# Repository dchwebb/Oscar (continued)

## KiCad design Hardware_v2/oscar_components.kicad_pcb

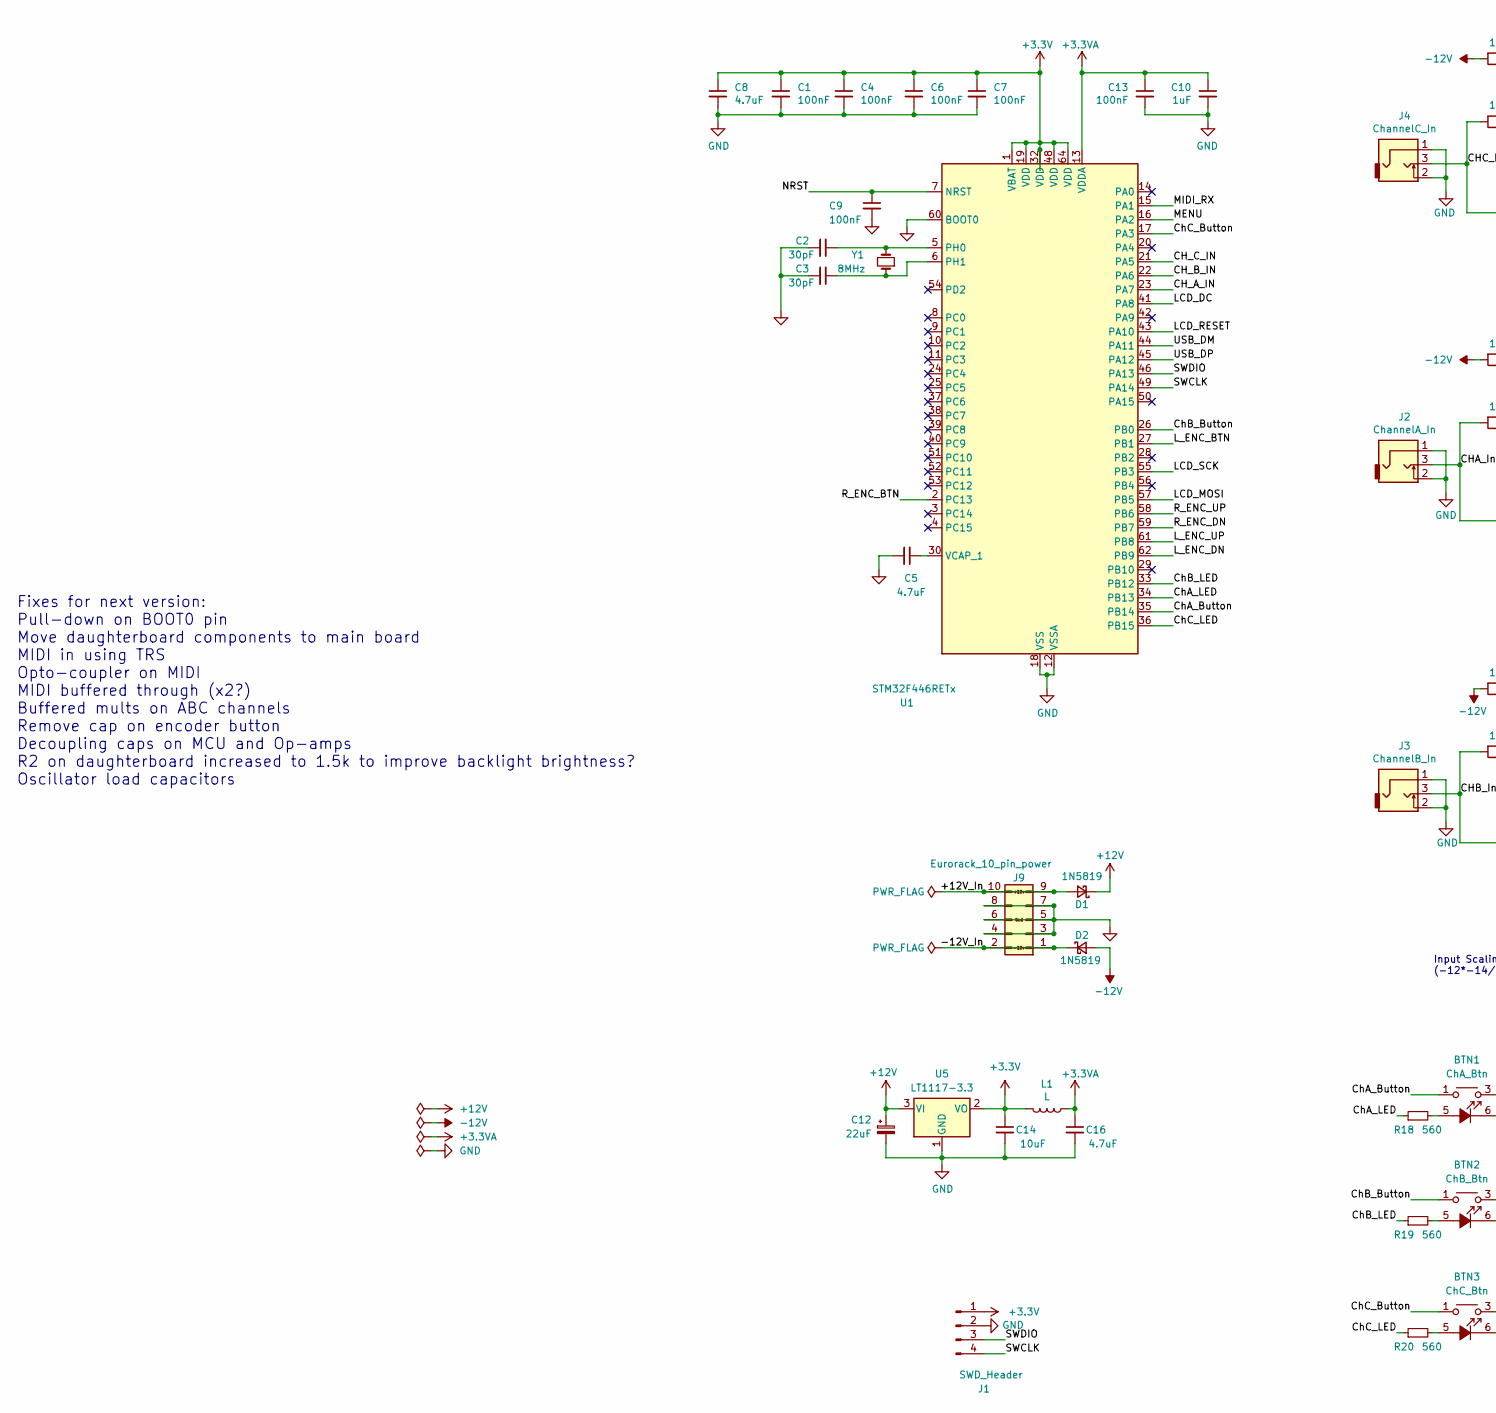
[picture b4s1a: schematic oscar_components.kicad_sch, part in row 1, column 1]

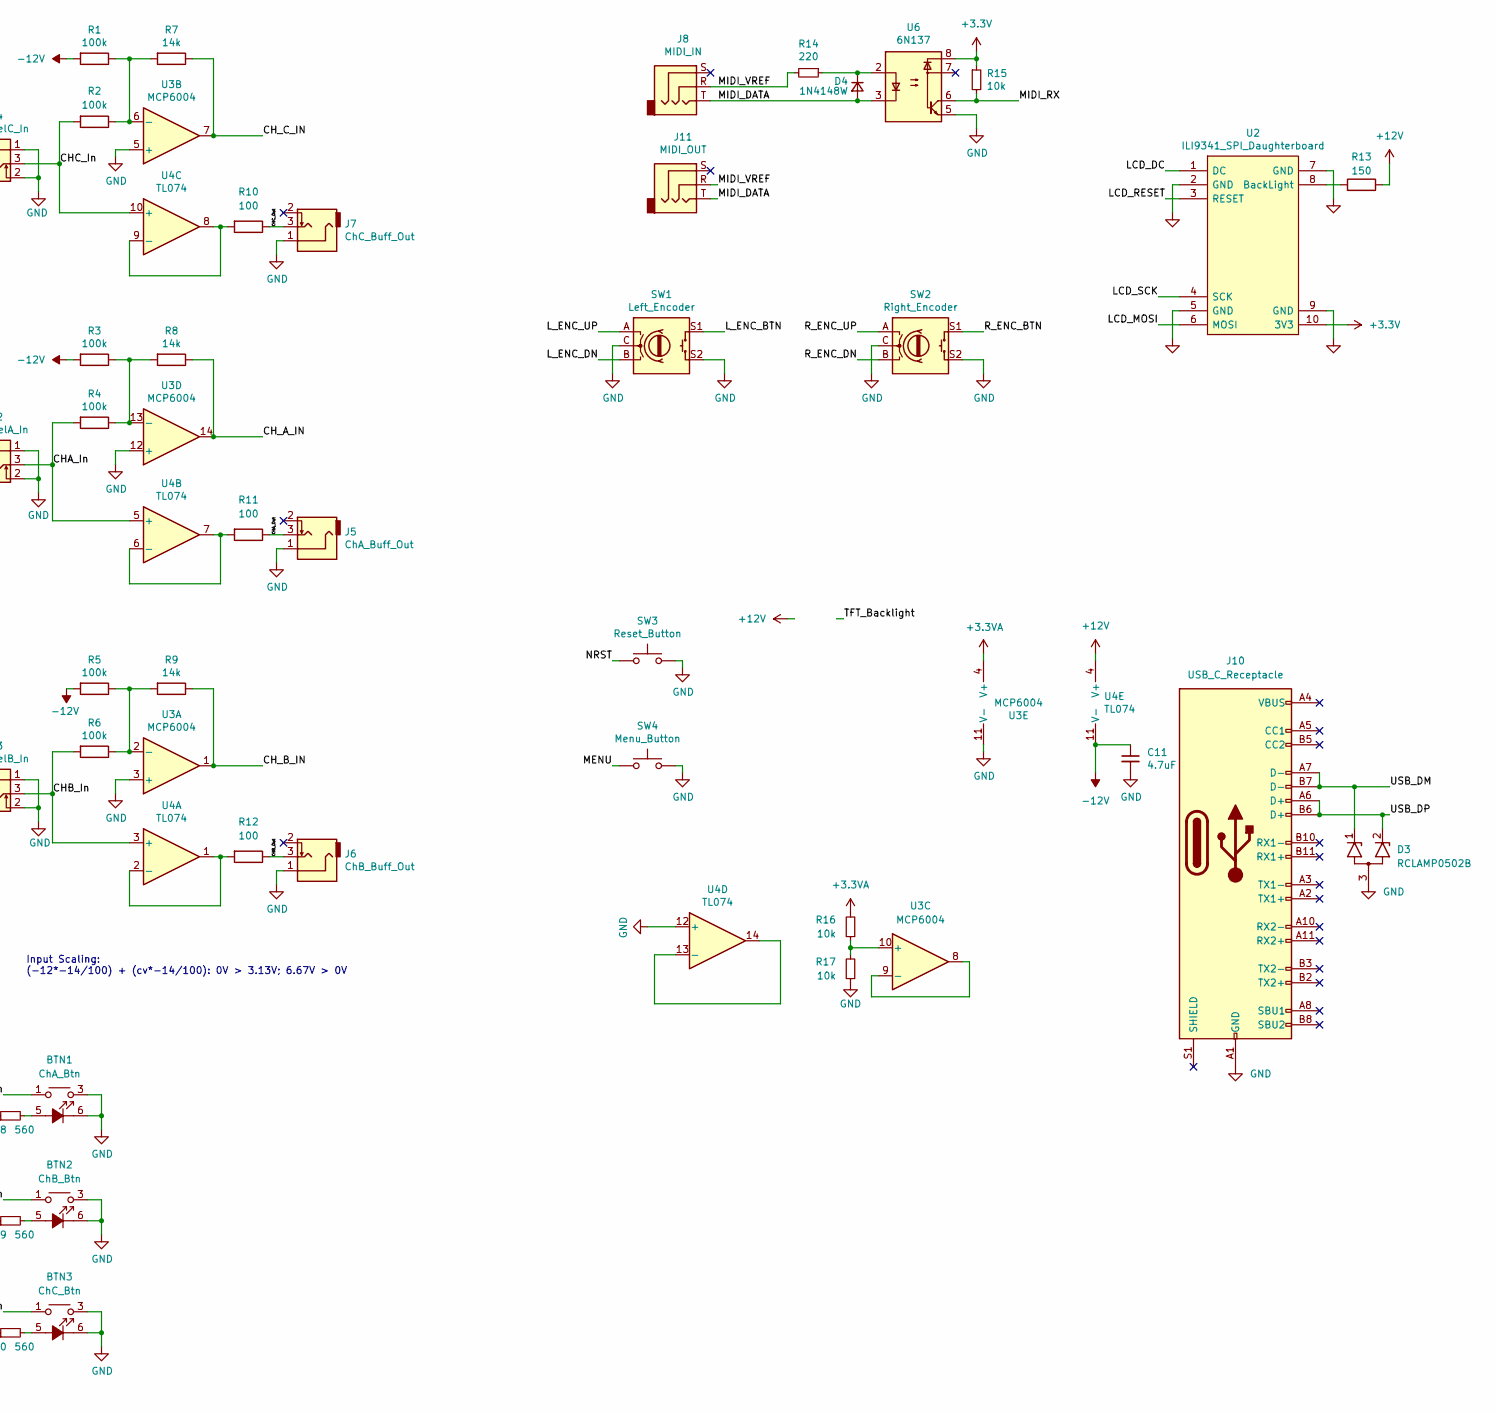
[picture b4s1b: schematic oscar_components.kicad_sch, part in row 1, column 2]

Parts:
BTN1: ChA_Btn; Low_Profile_LED_Button
BTN2: ChB_Btn; Low_Profile_LED_Button
BTN3: ChC_Btn; Low_Profile_LED_Button
C1, C4, C6, C7, C9, C13: 100nF; C_0805_2012Metric
C2, C3: 30pF; C_0805_2012Metric
C5, C8, C11, C16: 4.7uF; C_0805_2012Metric
C10: 1uF; C_0805_2012Metric
C12: 22uF; CP_Elec_4x5.8
C14: 10uF; CP_Elec_4x5.8
D1, D2: 1N5819; D_SOD-123
D3: RCLAMP0502B; SOT-416
D4: 1N4148W; D_SOD-123
J1: SWD_Header; SWD_header
J2: ChannelA_In; THONKICONN_hole
J3: ChannelB_In; THONKICONN_hole
J4: ChannelC_In; THONKICONN_hole
J5: ChA_Buff_Out; THONKICONN_hole
J6: ChB_Buff_Out; THONKICONN_hole
J7: ChC_Buff_Out; THONKICONN_hole
J8: MIDI_IN; Thonkiconn_Stereo-PJ366ST
J9: Eurorack_10_pin_power; Eurorack_10_pin_header
J10: USB_C_Receptacle; USB_C_Receptacle_Amphenol_12401951E412A
J11: MIDI_OUT; Thonkiconn_Stereo-PJ366ST
L1: L; R_0805_2012Metric
R1, R2, R3, R4, R5, R6: 100k; R_0805_2012Metric
R7, R8, R9: 14k; R_0805_2012Metric
R10, R11, R12: 100; R_0805_2012Metric
R13: 150; R_0805_2012Metric
R14: 220; R_0805_2012Metric
R15: 10k; R_0805_2012Metric
R16, R17: 10k; R_0805_2012Metric; Part_Number C23162
R18, R19, R20: 560; R_0805_2012Metric; Part_Number C23162
SW1: Left_Encoder; Encoder
SW2: Right_Encoder; Encoder
SW3: Reset_Button; SW_PUSH_6mm
SW4: Menu_Button; SW_PUSH_6mm
U1: STM32F446RETx; LQFP-64_10x10mm_P0.5mm
U2: ILI9341_SPI_Daughterboard; ILI9341_SPI_daughterboard_v2
U3: MCP6004; SOIC-14_3.9x8.7mm_P1.27mm
U4: TL074; SOIC-14_3.9x8.7mm_P1.27mm
U5: LT1117-3.3; SOT-223-3_TabPin2
U6: 6N137; DIP-8_W8.89mm_SMDSocket_LongPads
Y1: 8MHz; Crystal_SMD_Abracon_ABM3-2Pin_5.0x3.2mm

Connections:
+3.3V: C1.1, C4.1, C6.1, C7.1, C8.1, C14.1, J1.1, L1.2, R15.1, U1.1 (VBAT), U1.19 (VDD), U1.32 (VDD), U1.48 (VDD), U1.64 (VDD), U2.10 (3V3), U5.2 (VO), U6.8
+3.3VA: C10.1, C13.1, C16.1, L1.1, R16.2, U1.13 (VDDA), U3.4 (V+)
+12V: C12.1, D1.1 (K), R13.1, U4.4 (V+), U5.3 (VI)
-12V: C11.1, D2.2 (A), R1.2, R3.2, R5.2, U4.11 (V-)
/+12V_In: D1.2 (A), J9.9, J9.10
/-12V_In: D2.1 (K), J9.1, J9.2
/CHA_In: J2.3, R4.2, U4.5 (+)
/CHA_Out: J5.3, R11.1
/CHB_In: J3.3, R6.2, U4.3 (+)
/CHB_Out: J6.3, R12.1
/CHC_In: J4.3, R2.2, U4.10 (+)
/CHC_Out: J7.3, R10.1
/CH_A_IN: R8.1, U1.23 (PA7), U3.14
/CH_B_IN: R9.1, U1.22 (PA6), U3.1
/CH_C_IN: R7.1, U1.21 (PA5), U3.7
/ChA_Button: BTN1.1, BTN1.2, U1.35 (PB14)
/ChA_LED: R18.1, U1.34 (PB13)
/ChB_Button: BTN2.1, BTN2.2, U1.26 (PB0)
/ChB_LED: R19.1, U1.33 (PB12)
/ChC_Button: BTN3.1, BTN3.2, U1.17 (PA3)
/ChC_LED: R20.1, U1.36 (PB15)
/LCD_DC: U1.41 (PA8), U2.1 (DC)
/LCD_MOSI: U1.57 (PB5), U2.6 (MOSI)
/LCD_RESET: U1.43 (PA10), U2.3 (RESET)
/LCD_SCK: U1.55 (PB3), U2.4 (SCK)
/L_ENC_BTN: SW1.S1, U1.27 (PB1)
/L_ENC_DN: SW1.B, U1.62 (PB9)
/L_ENC_UP: SW1.A, U1.61 (PB8)
/MENU: SW4.1, U1.16 (PA2)
/MIDI_DATA: D4.2 (A), J8.T, J11.T, U6.3
/MIDI_RX: R15.2, U1.15 (PA1), U6.6
/MIDI_VREF: J8.R, J11.R, R14.2
/NRST: C9.1, SW3.1, U1.7 (NRST)
/R_ENC_BTN: SW2.S1, U1.2 (PC13)
/R_ENC_DN: SW2.B, U1.59 (PB7)
/R_ENC_UP: SW2.A, U1.58 (PB6)
/SWCLK: J1.4, U1.49 (PA14)
/SWDIO: J1.3, U1.46 (PA13)
/USB_DM: D3.1 (K1), J10.A7 (D-), J10.B7 (D-), U1.44 (PA11)
/USB_DP: D3.2 (K2), J10.A6 (D+), J10.B6 (D+), U1.45 (PA12)
GND: BTN1.3, BTN1.4, BTN1.6 (K), BTN2.3, BTN2.4, BTN2.6 (K), BTN3.3, BTN3.4, BTN3.6 (K), C1.2, C2.2, C3.2, C4.2, C5.2, C6.2, C7.2, C8.2, C9.2, C10.2, C11.2, C12.2, C13.2, C14.2, C16.2, D3.3 (A), J1.2, J2.1, J2.2, J3.1, J3.2, J4.1, J4.2, J5.1, J6.1, J7.1, J9.3, J9.4, J9.5, J9.6, J9.7, J9.8, J10.A1 (GND), J10.A12 (GND), J10.B1 (GND), J10.B12 (GND), R17.1, SW1.C, SW1.S2, SW2.C, SW2.S2, SW3.2, SW4.2, U1.12 (VSSA), U1.18 (VSS), U1.31 (VSS), U1.47 (VSS), U1.60 (BOOT0), U1.63 (VSS), U2.2 (GND), U2.5 (GND), U2.7 (GND), U2.9 (GND), U3.3 (+), U3.5 (+), U3.11 (V-), U3.12 (+), U4.12 (+), U5.1 (GND), U6.5
unnamed: BTN1.5 (A), R18.2
unnamed: BTN2.5 (A), R19.2
unnamed: BTN3.5 (A), R20.2
unnamed: D4.1 (K), R14.1, U6.2
unnamed: C2.1, U1.5 (PH0), Y1.2
unnamed: C3.1, U1.6 (PH1), Y1.1
unnamed: C5.1, U1.30 (VCAP_1)
unnamed: R13.2, U2.8 (BackLight)
unnamed: R5.1, R6.1, R9.2, U3.2 (-)
unnamed: R1.1, R2.1, R7.2, U3.6 (-)
unnamed: R16.1, R17.2, U3.10 (+)
unnamed: U3.8, U3.9 (-)
unnamed: R3.1, R4.1, R8.2, U3.13 (-)
unnamed: R12.2, U4.1, U4.2 (-)
unnamed: R11.2, U4.6 (-), U4.7
unnamed: R10.2, U4.8, U4.9 (-)
unnamed: U4.13 (-), U4.14

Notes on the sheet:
Input Scaling: (-12*-14/100) + (cv*-14/100): 0V > 3.13V; 6.67V > 0V
Fixes for next version: Pull-down on BOOT0 pin Move daughterboard components to main board MIDI in using TRS Opto-coupler on MIDI MIDI buffered through (x2?) Buffered mults on ABC channels Remove cap on encoder button Decoupling caps on MCU and Op-amps R2 on daughterboard increased to 1.5k to impro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

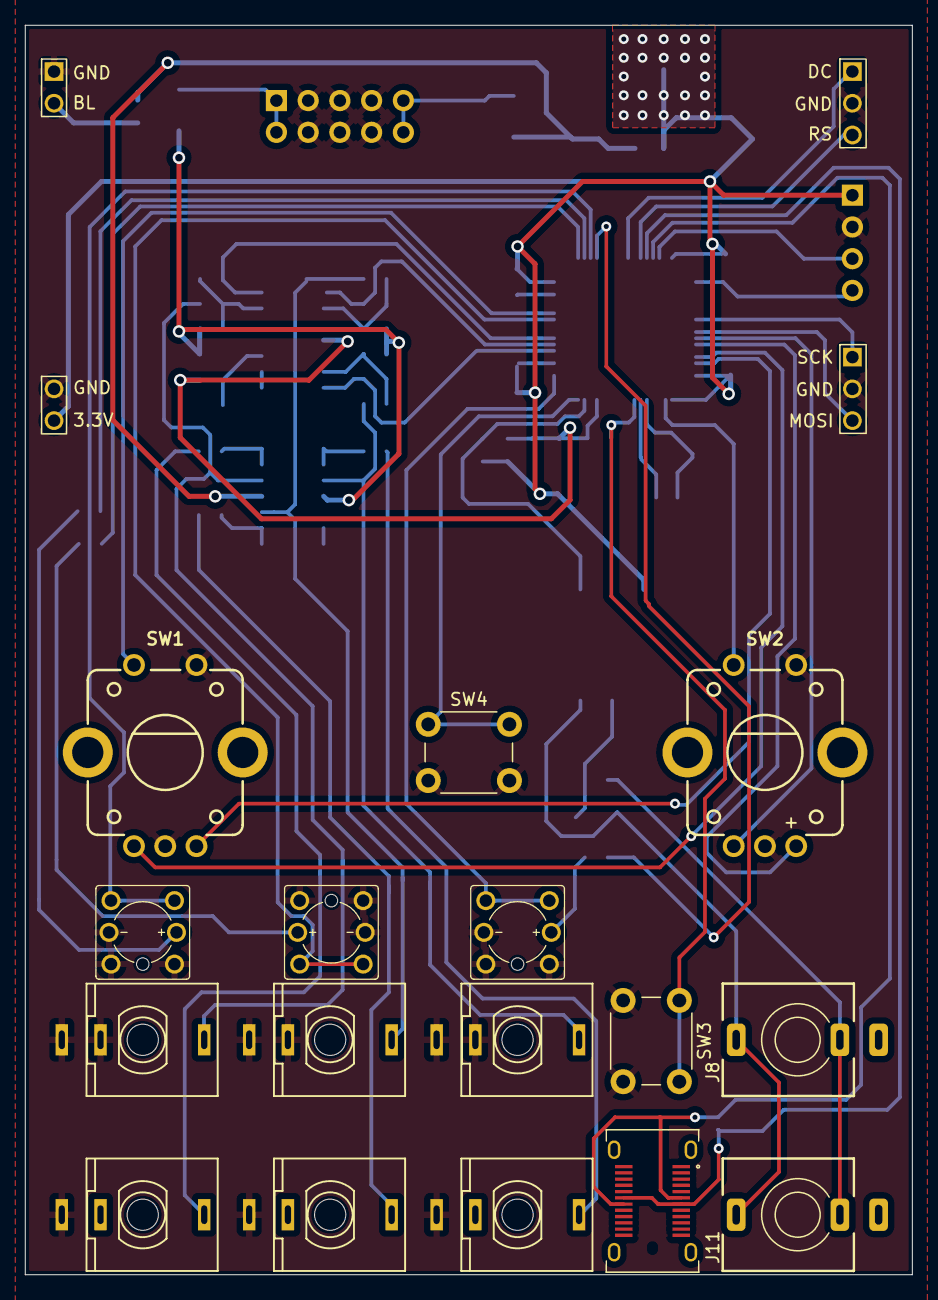
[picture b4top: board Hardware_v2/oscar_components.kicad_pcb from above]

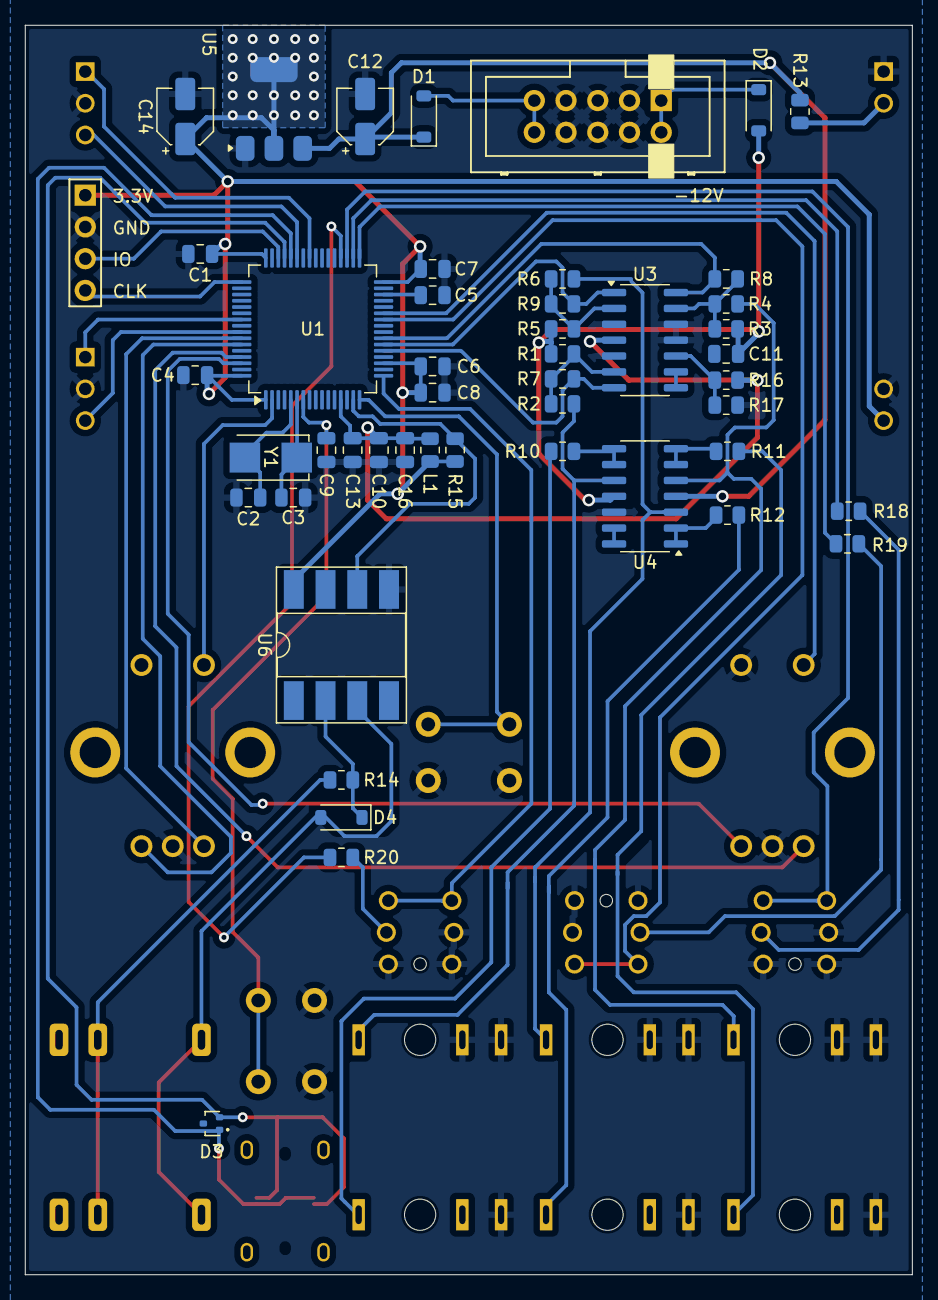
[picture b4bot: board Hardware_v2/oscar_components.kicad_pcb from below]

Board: 4 copper layers, 71.0 x 100.0 mm, 65 parts (48 on the bottom side), 58 nets.

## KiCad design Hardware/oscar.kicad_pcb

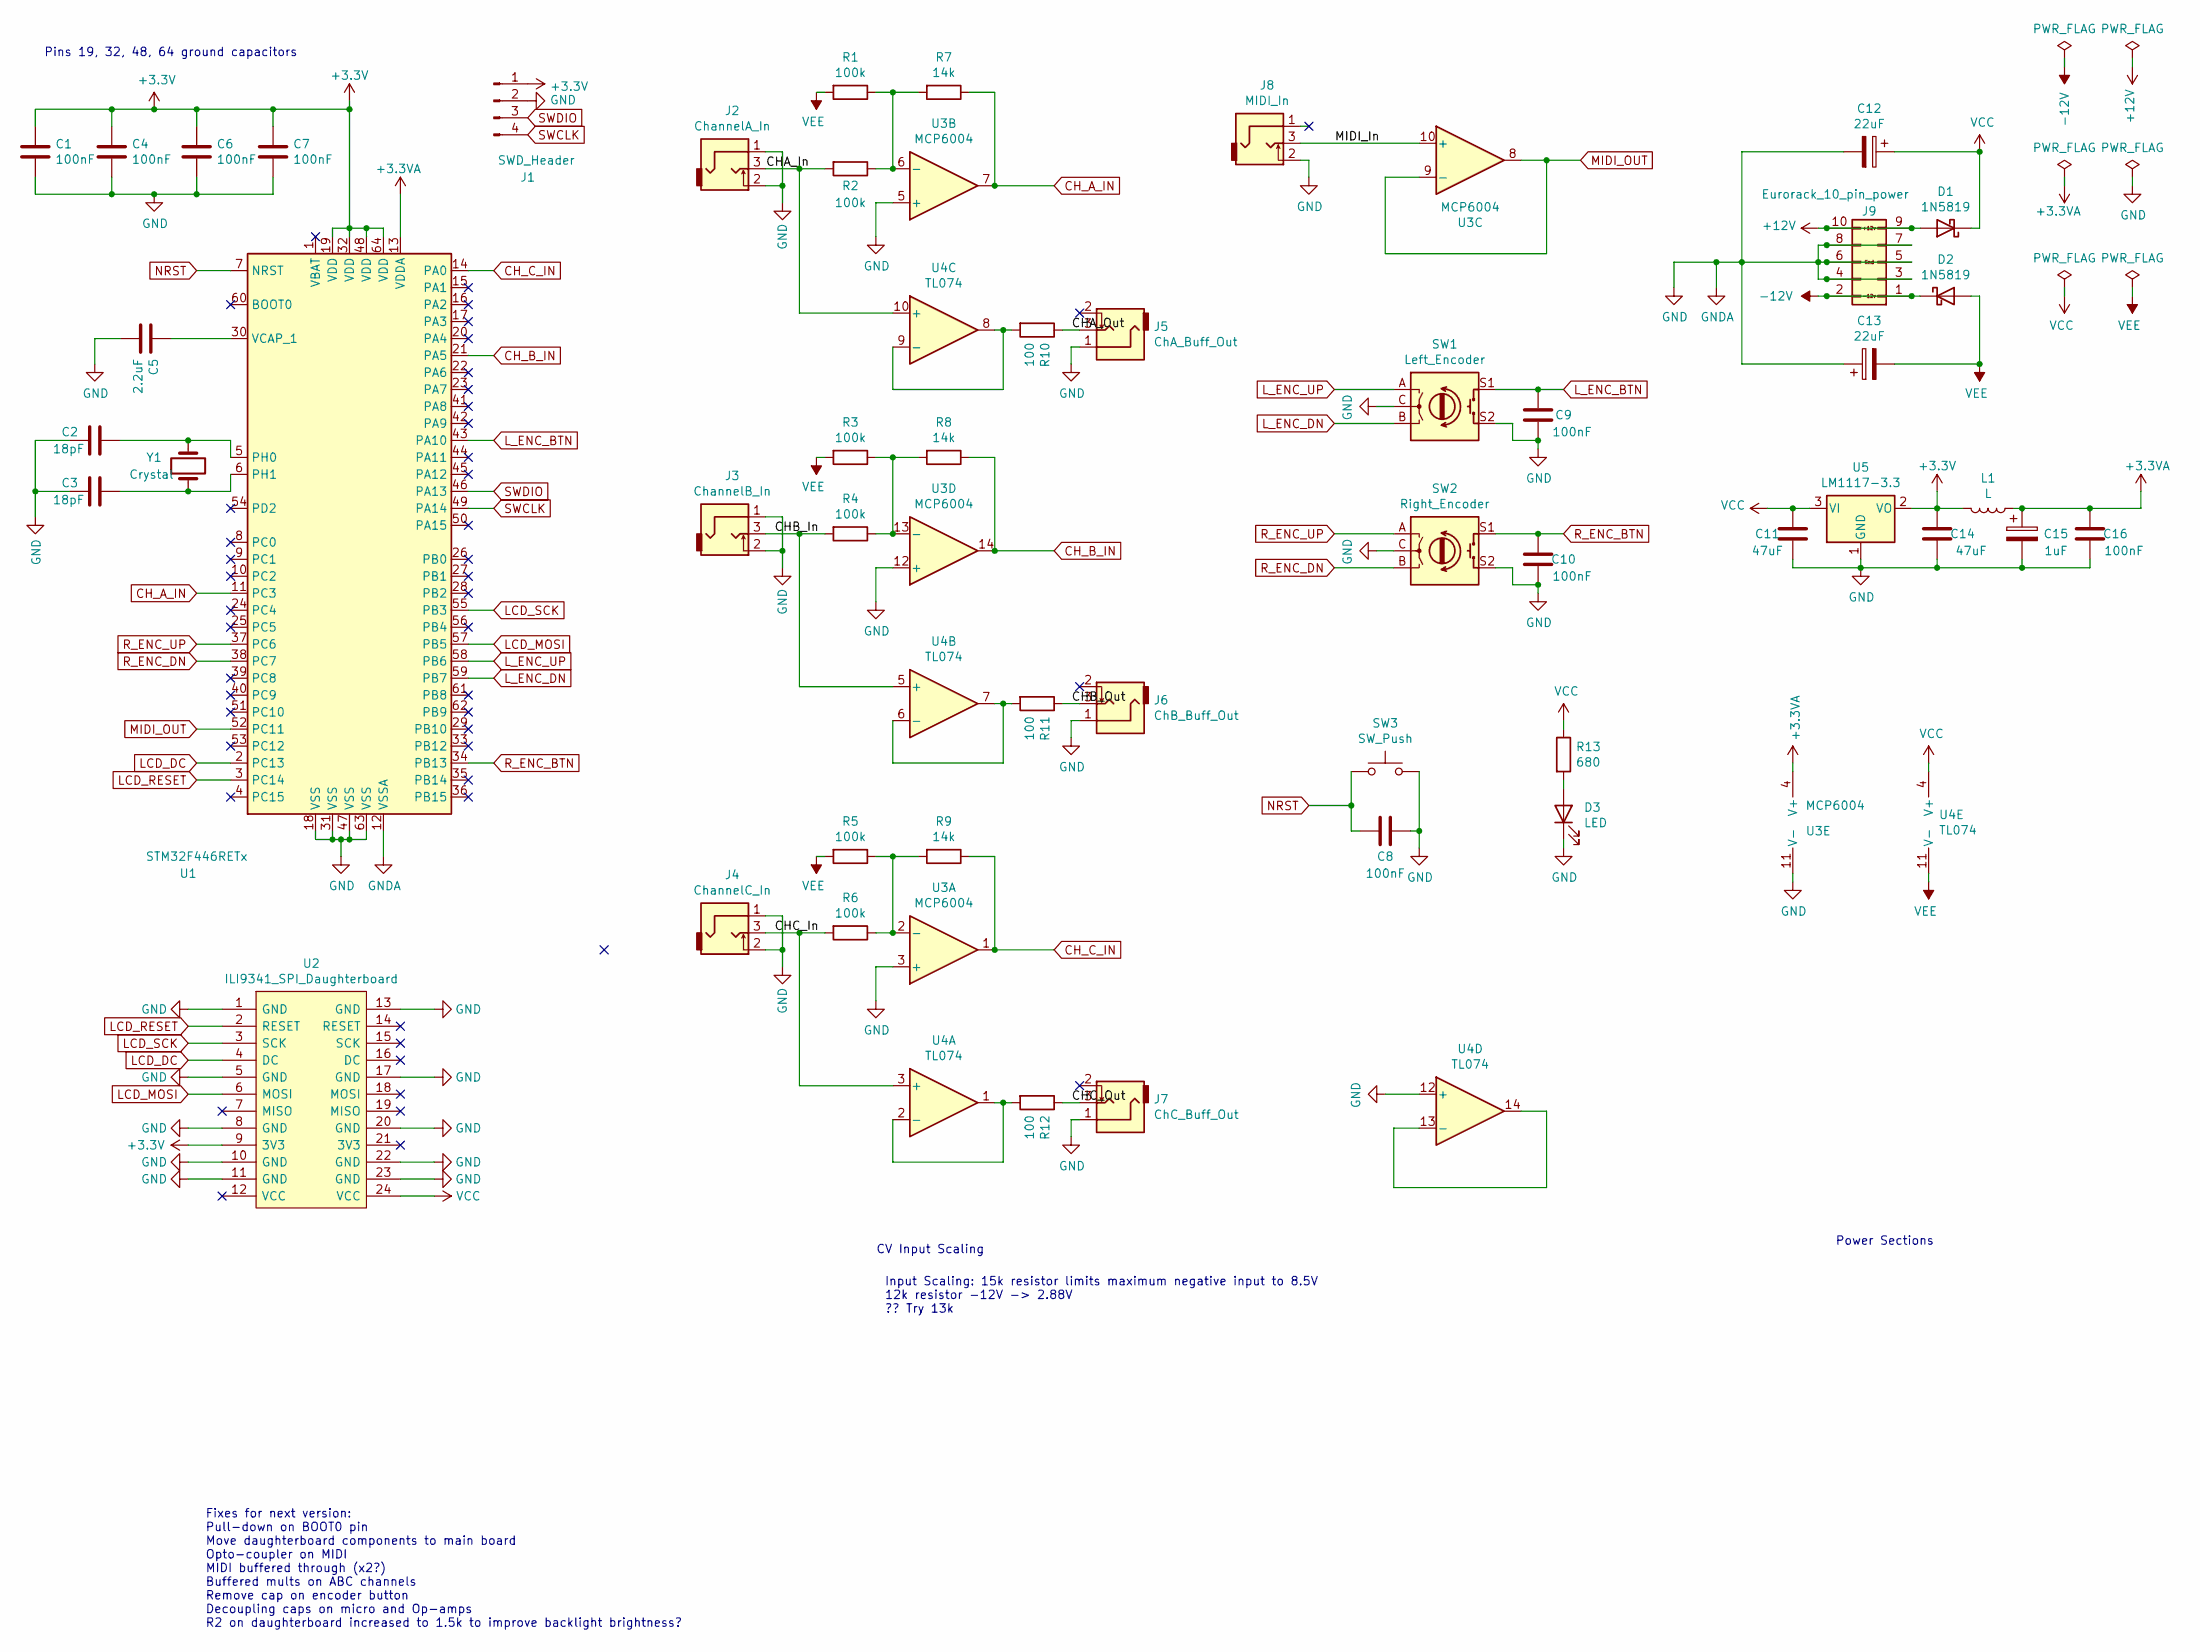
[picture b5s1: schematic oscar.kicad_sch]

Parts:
C1, C4, C6, C7, C8, C9, C10, C16: 100nF; C_0805_HandSoldering
C2, C3: 18pF; C_0805_HandSoldering
C5: 2.2uF; C_0805_HandSoldering
C11, C14: 47uF; CP_Elec_5x5.8
C12, C13: 22uF; CP_Elec_4x5.8
C15: 1uF; CP_Elec_4x5.8
D1, D2: 1N5819; D_SOD-123
D3: LED; LED_D5.0mm
J1: SWD_Header; SWD_header
J2: ChannelA_In; THONKICONN_hole
J3: ChannelB_In; THONKICONN_hole
J4: ChannelC_In; THONKICONN_hole
J5: ChA_Buff_Out; THONKICONN_hole
J6: ChB_Buff_Out; THONKICONN_hole
J7: ChC_Buff_Out; THONKICONN_hole
J8: MIDI_In; THONKICONN_hole
J9: Eurorack_10_pin_power; Eurorack_10_pin_header
L1: L; R_0805_HandSoldering
R1, R2, R3, R4, R5, R6: 100k; R_0805_HandSoldering
R7, R8, R9: 14k; R_0805_HandSoldering
R10, R11, R12: 100; R_0805_HandSoldering
R13: 680; R_0805_HandSoldering
SW1: Left_Encoder; Encoder
SW2: Right_Encoder; Encoder
SW3: SW_Push; SW_PUSH_6mm
U1: STM32F446RETx; LQFP-64_10x10mm_P0.5mm
U2: ILI9341_SPI_Daughterboard; ILI9341_SPI_daughterboard
U3: MCP6004; SOIC-14_N
U4: TL074; SOIC-14_N
U5: LM1117-3.3; TO-252-3_TabPin2
Y1: Crystal; Crystal_SMD

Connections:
+3.3VA: C15.1, C16.1, L1.1, U1.13 (VDDA), U3.4 (V+)
+3V3: C1.1, C4.1, C6.1, C7.1, C14.1, J1.1, L1.2, U1.19 (VDD), U1.32 (VDD), U1.48 (VDD), U1.64 (VDD), U2.9 (3V3), U5.2 (VO)
+12V: D1.2 (A), J9.9, J9.10
-12V: D2.1 (K), J9.1, J9.2
/CHA_In: J2.3, R2.2, U4.10 (+)
/CHA_Out: J5.3, R10.1
/CHB_In: J3.3, R4.2, U4.5 (+)
/CHB_Out: J6.3, R11.1
/CHC_In: J4.3, R6.2, U4.3 (+)
/CHC_Out: J7.3, R12.1
/MIDI_In: J8.3, U3.10 (+)
CH_A_IN: R7.1, U1.11 (PC3), U3.7
CH_B_IN: R8.1, U1.21 (PA5), U3.14
CH_C_IN: R9.1, U1.14 (PA0), U3.1
GND: C1.2, C2.2, C3.2, C4.2, C5.2, C6.2, C7.2, C8.1, C9.2, C10.2, C11.2, C12.2, C13.1, C14.2, C15.2, C16.2, D3.1 (K), J1.2, J2.1, J2.2, J3.1, J3.2, J4.1, J4.2, J5.1, J6.1, J7.1, J8.2, J9.3, J9.4, J9.5, J9.6, J9.7, J9.8, SW1.C, SW1.S2, SW2.C, SW2.S2, SW3.2, U1.12 (VSSA), U1.18 (VSS), U1.31 (VSS), U1.47 (VSS), U1.63 (VSS), U2.1 (GND), U2.5 (GND), U2.8 (GND), U2.10 (GND), U2.11 (GND), U2.13 (GND), U2.17 (GND), U2.20 (GND), U2.22 (GND), U2.23 (GND), U3.3 (+), U3.5 (+), U3.11 (V-), U3.12 (+), U4.12 (+), U5.1 (GND)
LCD_DC: U1.2 (PC13), U2.4 (DC)
LCD_MOSI: U1.57 (PB5), U2.6 (MOSI)
LCD_RESET: U1.3 (PC14), U2.2 (RESET)
LCD_SCK: U1.55 (PB3), U2.3 (SCK)
L_ENC_BTN: C9.1, SW1.S1, U1.43 (PA10)
L_ENC_DN: SW1.B, U1.59 (PB7)
L_ENC_UP: SW1.A, U1.58 (PB6)
MIDI_OUT: U1.52 (PC11), U3.8, U3.9 (-)
NRST: C8.2, SW3.1, U1.7 (NRST)
unnamed: C2.1, U1.5 (PH0), Y1.2
unnamed: C3.1, U1.6 (PH1), Y1.1
unnamed: C5.1, U1.30 (VCAP_1)
unnamed: D3.2 (A), R13.2
unnamed: R1.1, R2.1, R7.2, U3.6 (-)
unnamed: R3.1, R4.1, R8.2, U3.13 (-)
unnamed: R5.1, R6.1, R9.2, U3.2 (-)
unnamed: R10.2, U4.8, U4.9 (-)
unnamed: R11.2, U4.6 (-), U4.7
unnamed: R12.2, U4.1, U4.2 (-)
unnamed: U4.13 (-), U4.14
R_ENC_BTN: C10.1, SW2.S1, U1.34 (PB13)
R_ENC_DN: SW2.B, U1.38 (PC7)
R_ENC_UP: SW2.A, U1.37 (PC6)
SWCLK: J1.4, U1.49 (PA14)
SWDIO: J1.3, U1.46 (PA13)
VCC: C11.1, C12.1, D1.1 (K), R13.1, U2.24 (VCC), U4.4 (V+), U5.3 (VI)
VEE: C13.2, D2.2 (A), R1.2, R3.2, R5.2, U4.11 (V-)

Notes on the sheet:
CV Input Scaling
Fixes for next version: Pull-down on BOOT0 pin Move daughterboard components to main board Opto-coupler on MIDI MIDI buffered through (x2?) Buffered mults on ABC channels Remove cap on encoder button Decoupling caps on micro and Op-amps R2 on daughterboard increased to 1.5k to improve backlight bri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
Power Sections
Input Scaling: 15k resistor limits maximum negative input to 8.5V 12k resistor -12V -> 2.88V ?? Try 13k
Pins 19, 32, 48, 64 ground capacitors

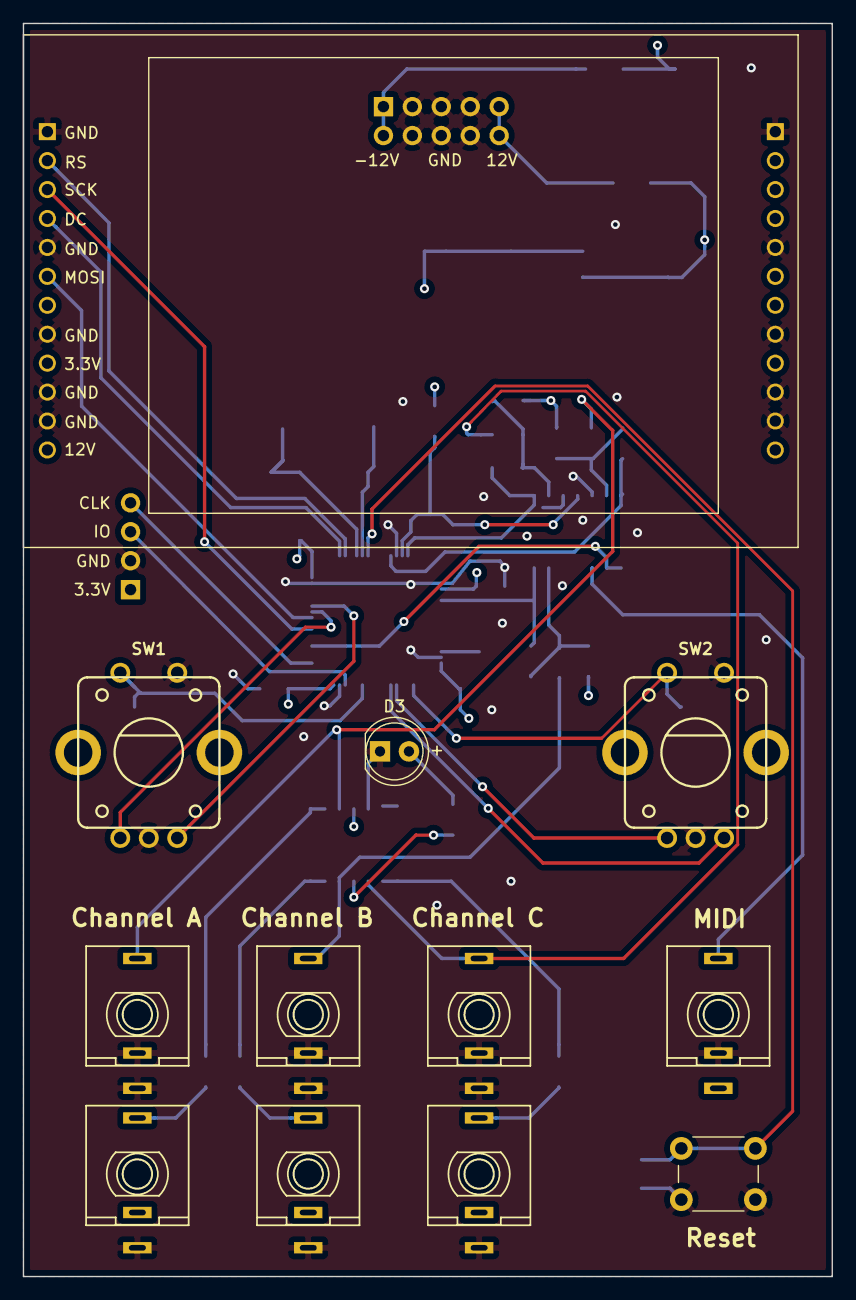
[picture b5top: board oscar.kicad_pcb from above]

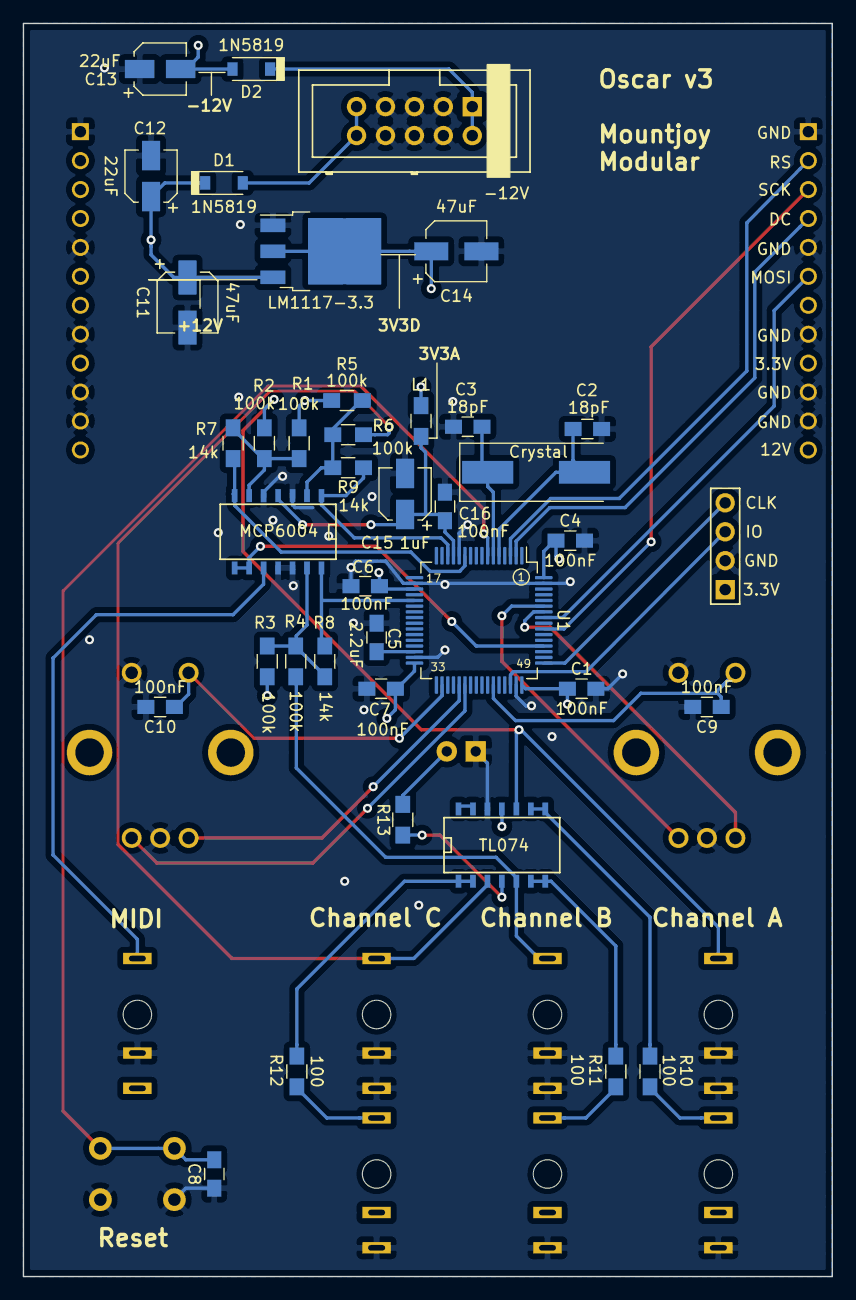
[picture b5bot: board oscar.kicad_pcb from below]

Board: 4 copper layers, 71.0 x 110.0 mm, 51 parts (39 on the bottom side), 42 nets.

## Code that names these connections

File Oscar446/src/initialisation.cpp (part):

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	RCC->AHB1ENR |= RCC_AHB1ENR_GPIOCEN;			// reset and clock control - advanced high performance bus - GPIO port C
	RCC->APB1ENR |= RCC_APB1ENR_SPI3EN;

	// Init DC (Data/Command) pin PC13
	GPIOC->MODER |= GPIO_MODER_MODER13_0;			// 00: Input (reset state)	01: General purpose output mode	10: Alternate function mode	11: Analog mode
	GPIOC->OSPEEDR |= GPIO_OSPEEDER_OSPEEDR13_0;		// Medium  - 00: Low speed; 01: Medium speed; 10: High speed; 11: Very high speed

	// Init RESET pin PC14
	GPIOC->MODER |= GPIO_MODER_MODER14_0;			// 00: Input (reset state)	01: General purpose output mode	10: Alternate function mode	11: Analog mode
	//GPIOC->PUPDR |= GPIO_PUPDR_PUPDR14_0;			// Pull up - 00: No pull-up, pull-down; 01 Pull-up; 10 Pull-down; 11 Reserved

	// PB5: SPI_MOSI [alternate function AF6]
	GPIOB->MODER |= GPIO_MODER_MODER5_1;			// 00: Input (reset state)	01: General purpose output mode	10: Alternate function mode	11: Analog mode
	GPIOB->OSPEEDR |= GPIO_OSPEEDER_OSPEEDR5;		// V High  - 00: Low speed; 01: Medium speed; 10: High speed; 11: Very high speed
	GPIOB->AFR[0] |= 0b0110 << 20;					// 0b0110 = Alternate Function 6 (SPI3); 20 is position of Pin 5

	// PB3 SPI_SCK [alternate function AF6]
	GPIOB->MODER |= GPIO_MODER_MODER3_1;			// 00: Input (reset state)	01: General purpose output mode	10: Alternate function mode	11: Analog mode
	GPIOB->OSPEEDR |= GPIO_OSPEEDER_OSPEEDR3;		// V High  - 00: Low speed; 01: Medium speed; 10: High speed; 11: Very high speed
	GPIOB->AFR[0] |= 0b0110 << 12;					// 0b0110 = Alternate Function 6 (SPI3); 12 is position of Pin 3
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	RCC->AHB1ENR |= RCC_AHB1ENR_GPIOCEN;
	RCC->APB2ENR |= RCC_APB2ENR_ADC1EN;

	// Enable ADC - PC3: ADC123_IN13; PA5: ADC12_IN5; PA0: ADC123_IN11
	GPIOC->MODER |= GPIO_MODER_MODER3;				// Set PC3 to Analog mode (0b11)
	GPIOA->MODER |= GPIO_MODER_MODER5;				// Set PA5 to Analog mode (0b11)
	GPIOA->MODER |= GPIO_MODER_MODER0;				// Set PA0 to Analog mode (0b11)

	ADC1->CR1 |= ADC_CR1_SCAN;						// Activate scan mode
	ADC1->SQR1 = (3 - 1) << 20;						// Number of conversions in sequence (set to 3, getting multiple samples for each channel to average)
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

void InitEncoders() {
	// L Encoder: button on PA10, up/down on PB6 and PB7; R Encoder: Button on PB13, up/down on PC6 and PC7
	RCC->AHB1ENR |= RCC_AHB1ENR_GPIOAEN;			// reset and clock control - advanced high performance bus - GPIO port A
	RCC->AHB1ENR |= RCC_AHB1ENR_GPIOBEN;			// reset and clock control - advanced high performance bus - GPIO port B
	RCC->AHB1ENR |= RCC_AHB1ENR_GPIOCEN;			// reset and clock control - advanced high performance bus - GPIO port C
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
	// 00: Input (reset state); 01: Output; 10: Alternate function; 11: Analog

	// configure PA10 Left encoder button
	GPIOA->PUPDR |= GPIO_PUPDR_PUPDR10_0;			// Set pin to pull up:  01 Pull-up; 10 Pull-down; 11 Reserved


	// configure PB13 right encoder button
	GPIOB->PUPDR |= GPIO_PUPDR_PUPDR13_0;			// Set pin to pull up:  01 Pull-up; 10 Pull-down; 11 Reserved

	// Debug code for using right encoder button as GPIO output
	//GPIOB->MODER |= GPIO_MODER_MODER13_0;			// For debug set pin to output

	// L Encoder using timer functionality - PB6 and PB7
	GPIOB->PUPDR |= GPIO_PUPDR_PUPDR6_0;			// Set pin to pull up:  01 Pull-up; 10 Pull-down; 11 Reserved
	GPIOB->MODER |= GPIO_MODER_MODER6_1;			// Set alternate function
	GPIOB->AFR[0] |= 2 << 24;						// Alternate function 2 is TIM4_CH1
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	TIM4->CNT = 32000;								// Start counter at mid way point
	TIM4->CR1 |= TIM_CR1_CEN;

	// R Encoder using timer functionality - PC6 and PC7
	GPIOC->PUPDR |= GPIO_PUPDR_PUPDR6_0;			// Set pin to pull up:  01 Pull-up; 10 Pull-down; 11 Reserved
	GPIOC->MODER |= GPIO_MODER_MODER6_1;			// Set alternate function
	GPIOC->AFR[0] |= 3 << 24;						// Alternate function 3 is TIM8_CH1
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
void InitUART()
{
	// PC11 UART4_RX 79
	// [PA1  UART4_RX 24 (AF8) ** NB Dev board seems to have something pulling this pin to ground so can't use]

	RCC->APB1ENR |= RCC_APB1ENR_UART4EN;			// UART4 clock enable

	GPIOC->MODER |= GPIO_MODER_MODER11_1;			// Set alternate function on PC11
	GPIOC->AFR[1] |= 0b1000 << 12;					// Alternate function on PC11 for UART4_RX is 1000: AF8

	int Baud = (SystemCoreClock / 4) / (16 * 31250);
	UART4->BRR |= Baud << 4;						// Baud Rate (called USART_BRR_DIV_Mantissa) = (Sys Clock: 180MHz / APB1 Prescaler DIV4: 45MHz) / (16 * 31250) = 90
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
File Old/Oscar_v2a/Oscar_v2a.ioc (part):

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Mcu.Name=STM32F446R(C-E)Tx
Mcu.Package=LQFP64
Mcu.UserName=STM32F446RETx
PA11.Mode=Device_Only
PA11.Signal=USB_OTG_FS_DM
PA12.Mode=Device_Only
PA12.Signal=USB_OTG_FS_DP
PB3.Mode=Simplex_Bidirectional_Master
PB3.Signal=SPI3_SCK
PB5.Mode=Simplex_Bidirectional_Master
PB5.Signal=SPI3_MOSI
PH0-OSC_IN.Mode=HSE-External-Oscillator
PH0-OSC_IN.Signal=RCC_OSC_IN
PH1-OSC_OUT.Mode=HSE-External-Oscillator
PH1-OSC_OUT.Signal=RCC_OSC_OUT
RCC.HSE_VALUE=8000000
RCC.SYSCLKFreq_VALUE=180000000
RCC.SYSCLKSource=RCC_SYSCLKSOURCE_PLLCLK
board=custom

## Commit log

2019-04-18 Switched from ADC2 to ADC1
2019-04-19 Created LCD display class
2019-04-20 Updates to LCD Class
2019-04-20 draw character uses DMA/SPI
2019-04-24 Added fourier transform test scripts
2019-04-25 Added FFT
2019-04-26 FFT optimisations
2019-04-27 Fixes to trigger mode stability; first draft of FFT from samples
2019-04-28 FFT working on ADC data
2019-04-29 Added switching between FFT and oscilloscope
2019-04-29 Refactoring and array clean up
2019-04-30 Includes various techniques for optimising drawing of FFT
2019-05-01 Fixed issues in oscilloscode triggering at high speeds and cleaned up FFT draw code
2019-05-02 Code cleanup; Encoders with debouncing
2019-05-04 Refactor including moving fft to new class; speed up sample capture
2019-05-04 Rough draft of FFT autotune
2019-05-06 FFT autotune mode
2019-05-06 FFT autotune colouring
2019-05-06 Implemented character and string memory write
2019-05-07 FFT DIsplay colour codes main harmonics and provides detail on frequency and harmonic number
2019-05-07 refactor UI class; started oscilloscope scaling
2019-05-10 added calibration and voltage scaling for oscilloscope
    Moved various functions to UI class
    Added frequency calculation on oscilloscope
2019-05-10 Refactoring class names
2019-05-10 Show frequency on oscilloscpe and optimise string drawing
2019-05-12 Implemented basic waterfall plot
2019-05-12 Waterfall plot implemented (not yet using display buffers)
2019-05-14 Waterfall plot works with frame buffers
2019-05-15 Clean up of waterfall plot mode
2019-05-18 Error handling in FFT; Reworked menu operations
2019-05-20 Added option to select channel for FFT analysis
2019-05-22 Added basic circular oscilloscope mode functionality
2019-05-23 Second revision of circular mode using cosine LUT and better tuning
2019-06-01 Further refinements to Circular mode
2019-06-01 Continuous circular mode implemented
2019-06-02 Improve tuning algorithm in circular mode
2019-06-04 Added option to change capture channel in Circular mode
2019-06-04 Minor tweaks
2019-06-11 Added some basic MIDI decoding functionality
2019-06-12 Added control change to MIDI handler
2019-06-16 MIDI smart draw mode implemented
2019-06-17 First draft of setup menu
2019-06-18 Added software debouncing for encoders and buttons; more work on menu
2019-06-19 Further work on setup menus
2019-06-19 Minor menu enhancements
2019-06-19 UI tweaks and variable/property tidying
2019-06-27 Added third channel
2019-07-11 Hardware reorganisation
2019-07-12 Updated Encoders to use Timers
2019-07-12 Further hardware abstraction and moved interrupts
2019-07-12 Updated LCD class
2019-07-12 Merged in remaining functions including block based Osc display
2019-07-19 First draft of PCB layout
2019-07-20 Better scaling for horizontal zoom; 4 layer board updates
2019-07-22 MIDI uses ring buffer instead of queu and added clock
2019-07-23 Added LCD Solder pads
2019-07-23 increased size of power traces
2019-07-28 v1 PCB; added zero crossing count config to Circular mode; refactored variables into objects
2019-07-29 Refactored Draw Buffers
2019-08-07 Added handling for drawing oscilloscope when trigger not activated
2019-08-12 Minor refactor
2019-08-17 Created LCD daughterboard
2019-09-04 PCB Updated to incorporate LCD daughterboard
2019-09-06 Added panel PCB
2019-09-07 Updates to panel PCB
2019-09-08 updated codebase
2019-11-09 Reorganised and relocated reposistory
2020-02-08 Increased oscillator max voltage from 8V to 12V; fixes to FFT menu (allows channel select in config)
2020-02-08 Trigger channel intelligently selected based on preference and channel visibility
2020-02-09 Config now stores Trigger channel preference
2020-02-09 emoved redundant development code
2020-02-09 Cleaned up extern and volatile
2020-02-09 Cleanup pass
2020-02-09 Reversed direction of zoom encoders; added option to vertically scale overlay in FFT
    Also increased maximum oscillator window time to ~2s
2020-06-03 FFT Mode channel select reverse direction fixed; converted project to CubeIDE
2021-09-23 Debug build
2022-03-31 Updates to Kicad 6
2023-03-13 Testing sample timer resolution changes
2023-03-13 Increased sample capture resolution by reducing speed of prescaler
2023-03-14 Cleaned unused and old driver files
2023-03-14 Fixed bug in oscillator drawing function
2023-03-14 Started cleaning FFT class
2023-03-14 Further clean up of fft class
2023-03-14 Updated FFT auto-tune routine
2023-03-14 Refactoring
2023-03-14 Fixed bug in harmonicFreq() function incorrectly truncating large frequencies
2023-03-15 Refactoring DRAWBUFFERWIDTH
2023-03-15 Refactored lcd.drawBuffer
2023-03-15 Fixed bug using right encoder button in mode with no menu
2023-03-15 Refactoring FFT and osc classes
2023-03-15 Refactoring buffer number vairiables
2023-03-15 Refactoring osc class
2023-03-15 Upgraded to C++ 20
2023-03-15 Refactoring UI class
2023-03-15 Disable circular mode
2023-03-15 Reworked encoder button handling to avoid using interrupts and improve debouncing
2023-03-15 Completely removed references to circular mode
2023-03-15 Fixed bug drawing fft overlay offset by 1
2023-03-15 FFT 1st harmonic drawn in larger font
2023-03-16 Refactoring FFT class
2023-03-16 General refactoring and clean up
2023-03-16 Reworked MIDI monitor to use circular buffers rather than deques
2023-03-16 Refactored MIDI class
2023-03-17 Minor clean up
2023-03-17 Fixed buffer overflow in osc;
    const updates and space saving to lcd class
    fft class uses constexpr sine look up table
2023-03-17 Added readme and graphics
2023-03-17 Corrections to ReEadme and ioc file
2023-03-22 Update notes in schematic
2023-03-31 Started adding tuner functionality
2023-04-01 Basic zero crossing tuner implementation
2023-04-01 Allow pitch detection where multiple zero crossings in cycle
2023-04-01 Started adding plumbing for auto-correlation
2023-04-02 Auto-correlation working
2023-04-03 Refactored FFT class to improve separation of fft calculation
2023-04-03 Added sample capture to tuner FFT mode
2023-04-04 Initial FFT tuner calculation done
2023-04-04 Added phase debug information
2023-04-05 Added test code for FFT phase adjustment experiments
2023-04-07 Tuner FFT phase adjustment working
2023-04-07 Improved accuracy of FFT tuner at higher frequencies
    Display note name and error in cents
2023-04-10 Removed auto-correlation mode from tuner
2023-04-10 Clean up of tuner code
2023-04-11 Fine tuning tuner issues
2023-06-11 Added potential fix for overflow bug in FFT
2023-07-09 Added trace overlay to tuner mode
2023-07-09 Tuner config saving enabled; Added overlay on/off control
2023-07-10 Rewrote config handling
2023-07-10 Added vertical scaling to tuner overlay; tidied up includes
2023-09-14 Tweaks to tuner
2024-07-12 Fixed inverted tuner wave overlay
2024-12-16 Fixed bug with MIDI off events being lost; added reverse encoder option
2024-12-16 Updated builds
2025-03-31 Started creating v2 hardware; added construction images
2025-04-03 Routing of component board
2025-04-03 Folder reorganisation
2025-04-03 PCB Layout
2025-04-05 Started working on panel
2025-04-06 Control Layout change
2025-04-07 Started adding JLC part numbers; changed optocoupler to H11L1
2025-04-12 More layout
2025-04-13 Started updating firmware to v2a
2025-04-14 V3 production files submitted to JLC
2025-04-15 Started creating v3 firmware
2025-04-15 Added watchdog code and access to backup SRAM
2025-04-16 Updated to RGB colour handling
2025-04-17 Backup before performance testing
2025-04-23 Starting v3 hardware revision
2025-04-27 USB working
2025-04-27 Schematic annotation
2025-04-28 Buttons and LEDs working correctly
2025-05-12 Implemented channel selection buttons
2025-05-13 Selectively update oscilloscope voltage
2025-05-16 New 3.1 daughterboard layout
2025-05-19 Updated LED resistor values
2025-05-23 Fixes to oscilloscope draw in block mode
2025-05-24 Fixes to oscilloscope draw routine
2025-05-27 Oscilloscope fixes
2025-06-03 Updated text position constants
2025-06-03 Reverting oscilloscope performance testing
2025-06-03 Fixed text centering in tuner mode
2025-06-04 Minor tweaks to tuner
2025-06-04 USB MIDI event display working
2025-06-05 Fixes to interleaved serial and USB MIDI data
2025-06-06 USB bootloader working
2025-06-07 UI fixes; minor tweaks to v3.2 LCD daughterboard
2025-06-07 Starting to add system menu
2025-06-09 Clean up system menu code
2025-06-10 Increased time of longest oscilloscope capture; updates to triggering
2025-06-11 Fixes to oscilloscope frequency estimation
2025-06-11 Tweaks to Tuner No Signal code
2025-06-12 Oscilloscope triggers on rising edge (previously falling)
2025-06-12 Started adding documentation
    MIDI events do not fade completely to black
2025-06-13 Uploaded zipped gerbers
2025-06-14 Work on Build Guide; Clean up old folders
2025-06-14 Create LICENSE
2025-06-17 Updated build guide
2025-06-23 Updates to build guide and readme
2025-06-24 Switch off channel button LEDs in MIDI mode
2025-06-25 Added graphics to manual
2025-06-25 Documentation updates
2025-06-26 Updated sample time defaults on oscilloscope
    + add clear config command to serial console
2025-07-06 Updates to manual
2025-07-10 Update LICENSE
2025-07-25 Increased size of regulator heat sink vias
